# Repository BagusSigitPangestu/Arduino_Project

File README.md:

# Arduino Project

Repository ini berisi beberapa proyek Arduino yang telah dibuat selama kuliah.

## 🔧 Tips Mengatasi Port Arduino Tidak Terdeteksi di Linux

Jika port serial tidak terdeteksi saat menggunakan Arduino di Linux, coba jalankan perintah berikut secara berurutan:

### 1️⃣ Hapus Udev Rules yang Bermasalah
Jalankan perintah berikut untuk menghapus aturan `udev` yang dapat menyebabkan konflik:
```bash
for f in /usr/lib/udev/rules.d/*brltty*.rules; do
    sudo ln -s /dev/null "/etc/udev/rules.d/$(basename "$f")"
done
sudo udevadm control --reload-rules
```

### 2️⃣ Nonaktifkan Layanan `brltty`
Nonaktifkan `brltty` (Braille Terminal Daemon) yang dapat mengganggu koneksi serial:
```bash
sudo systemctl mask brltty.path
```

### 3️⃣ Tambahkan Pengguna ke Grup `dialout`
Pastikan akun pengguna memiliki akses ke perangkat serial dengan menambahkan ke grup `dialout`:
```bash
sudo usermod -a -G dialout $USER
```
Setelah itu, logout dan login kembali agar perubahan diterapkan.

---

📌 **Referensi:**  
[Unable to use USB dongle based on USB-serial converter](https://unix.stackexchange.com/questions/670636/unable-to-use-usb-dongle-based-on-usb-serial-converter-chip/670637#670637)

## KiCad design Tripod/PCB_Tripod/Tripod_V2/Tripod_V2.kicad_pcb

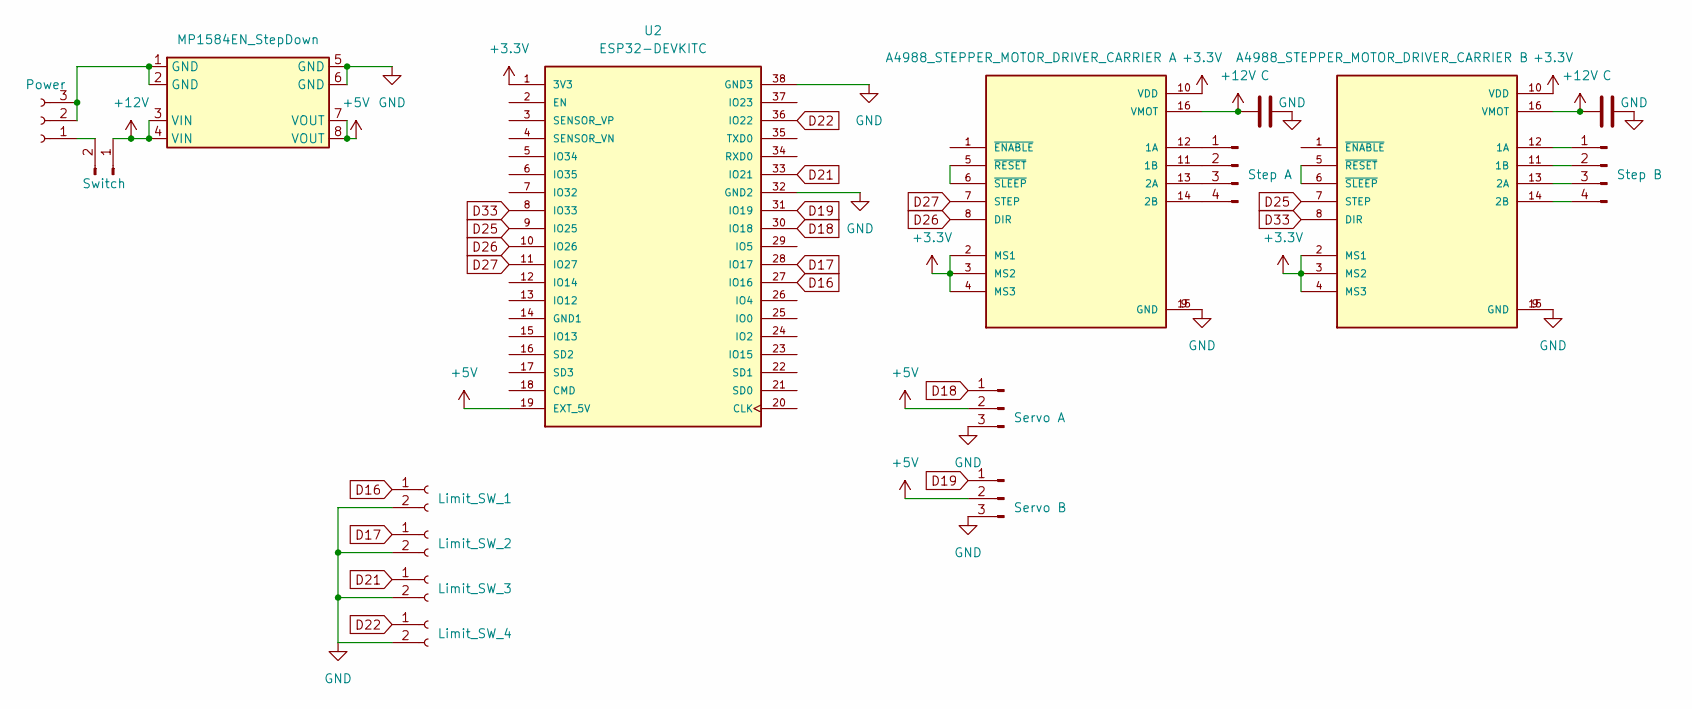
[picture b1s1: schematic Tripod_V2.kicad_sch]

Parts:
C1, C2: C; CP_Radial_D5.0mm_P2.50mm
J1: Power; BarrelJack_Horizontal
J2: Switch; TE_282837-2
J3: Servo A; PinHeader_1x03_P2.54mm_Vertical
J4: Servo B; PinHeader_1x03_P2.54mm_Vertical
J5: Step A; JST_EH_B4B-EH-A_1x04_P2.50mm_Vertical
J6: Step B; JST_EH_B4B-EH-A_1x04_P2.50mm_Vertical
J7: Limit_SW_1; PinHeader_1x02_P2.54mm_Vertical
J8: Limit_SW_2; PinHeader_1x02_P2.54mm_Vertical
J9: Limit_SW_3; PinHeader_1x02_P2.54mm_Vertical
J10: Limit_SW_4; PinHeader_1x02_P2.54mm_Vertical
U1: MP1584EN_StepDown
U2: ESP32-DEVKITC; MODULE_ESP32-DEVKITC; PARTREV N/A
U3: A4988_STEPPER_MOTOR_DRIVER_CARRIER A; MODULE_A4988_STEPPER_MOTOR_DRIVER_CARRIER
U4: A4988_STEPPER_MOTOR_DRIVER_CARRIER B; MODULE_A4988_STEPPER_MOTOR_DRIVER_CARRIER

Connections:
+3V3: U2.1 (3V3), U3.2 (MS1), U3.3 (MS2), U3.4 (MS3), U3.10 (VDD), U4.2 (MS1), U4.3 (MS2), U4.4 (MS3), U4.10 (VDD)
+5V: J3.2, J4.2, U1.7 (VOUT), U1.8 (VOUT), U2.19 (EXT_5V)
+12V: C1.1, C2.1, J2.1, U1.3 (VIN), U1.4 (VIN), U3.16 (VMOT), U4.16 (VMOT)
D16: J7.1, U2.27 (IO16)
D17: J8.1, U2.28 (IO17)
D18: J3.1, U2.30 (IO18)
D19: J4.1, U2.31 (IO19)
D21: J9.1, U2.33 (IO21)
D22: J10.1, U2.36 (IO22)
D25: U2.9 (IO25), U4.7 (STEP)
D26: U2.10 (IO26), U3.8 (DIR)
D27: U2.11 (IO27), U3.7 (STEP)
D33: U2.8 (IO33), U4.8 (DIR)
GND: C1.2, C2.2, J3.3, J4.3, J7.2, J8.2, J9.2, J10.2, U1.5 (GND), U1.6 (GND), U2.32 (GND2), U2.38 (GND3), U3.9 (GND), U3.15 (GND), U4.9 (GND), U4.15 (GND)
unnamed: J1.1, J2.2
unnamed: J1.2, J1.3, U1.1 (GND), U1.2 (GND)
unnamed: J5.1, U3.12 (1A)
unnamed: J5.2, U3.11 (1B)
unnamed: J5.3, U3.13 (2A)
unnamed: J5.4, U3.14 (2B)
unnamed: J6.1, U4.12 (1A)
unnamed: J6.2, U4.11 (1B)
unnamed: J6.3, U4.13 (2A)
unnamed: J6.4, U4.14 (2B)
unnamed: U3.5 (~RESET), U3.6 (~SLEEP)
unnamed: U4.5 (~RESET), U4.6 (~SLEEP)

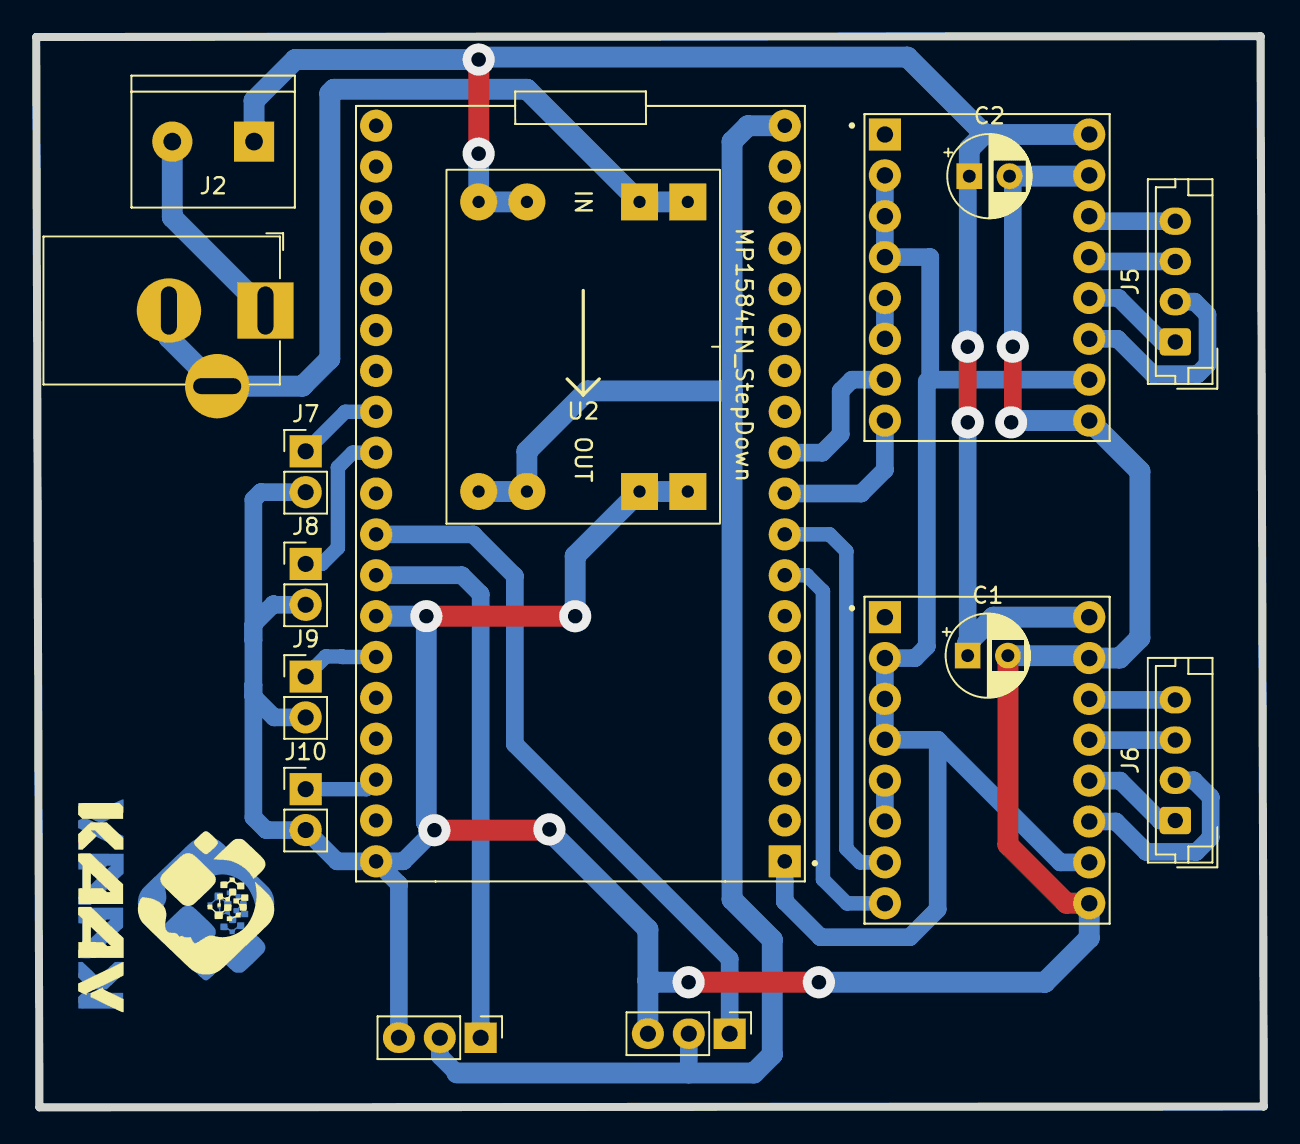
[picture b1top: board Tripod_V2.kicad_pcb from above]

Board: 2 copper layers, 76.3 x 66.6 mm, 16 parts (0 on the bottom side), 26 nets.

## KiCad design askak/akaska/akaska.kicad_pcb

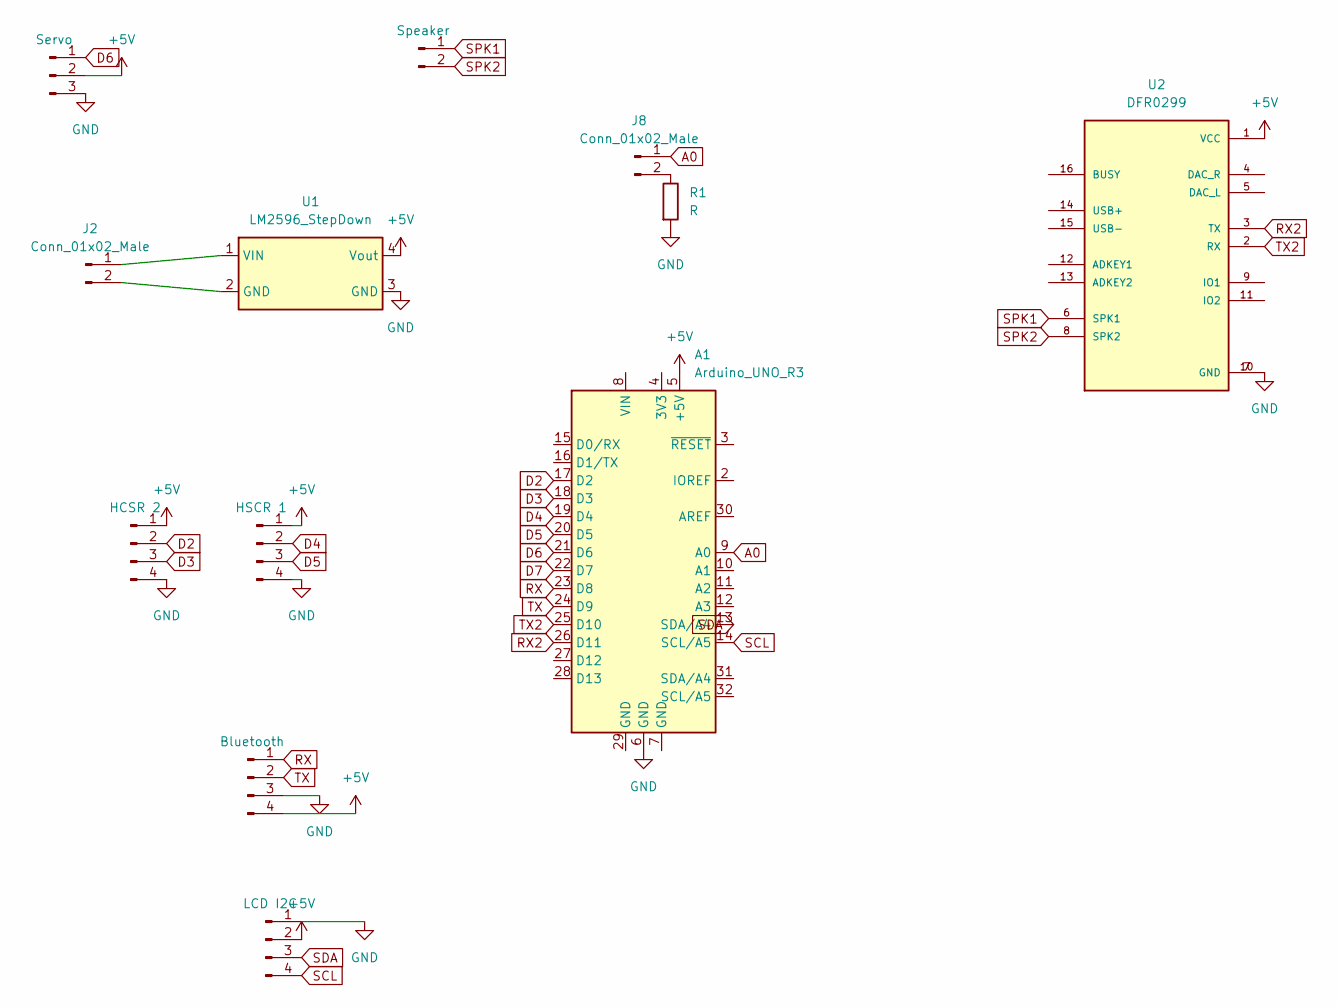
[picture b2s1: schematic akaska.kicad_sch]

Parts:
A1: Arduino_UNO_R3
J1: Servo; PinHeader_1x03_P2.54mm_Vertical
J2: Conn_01x02_Male; TerminalBlock_Altech_AK300-2_P5.00mm
J3: HCSR 2; PinHeader_1x04_P2.54mm_Vertical
J4: Bluetooth; PinSocket_1x04_P2.54mm_Vertical
J5: HSCR 1; PinHeader_1x04_P2.54mm_Vertical
J6: LCD I2C; PinHeader_1x04_P2.54mm_Vertical
J7: Speaker; PinHeader_1x02_P2.54mm_Vertical
J8: Conn_01x02_Male; LED_D3.0mm
R1: R; R_Axial_DIN0207_L6.3mm_D2.5mm_P15.24mm_Horizontal
U1: LM2596_StepDown; StepDown_LM2596
U2: DFR0299; MODULE_DFR0299

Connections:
+5V: A1.5 (+5V), J1.2, J3.1, J4.4, J5.1, J6.2, U1.4 (Vout), U2.1 (VCC)
A0: A1.9 (A0), J8.1
D2: A1.17 (D2), J3.2
D3: A1.18 (D3), J3.3
D4: A1.19 (D4), J5.2
D5: A1.20 (D5), J5.3
D6: A1.21 (D6), J1.1
D7: A1.22 (D7)
GND: A1.6 (GND), J1.3, J3.4, J4.3, J5.4, J6.1, R1.2, U1.3 (GND), U2.7 (GND), U2.10 (GND)
unnamed: J2.1, U1.1 (VIN)
unnamed: J2.2, U1.2 (GND)
unnamed: J8.2, R1.1
RX: A1.23 (D8), J4.1
RX2: A1.26 (D11), U2.3 (TX)
SCL: A1.14 (SCL/A5), J6.4
SDA: A1.13 (SDA/A4), J6.3
SPK1: J7.1, U2.6 (SPK1)
SPK2: J7.2, U2.8 (SPK2)
TX: A1.24 (D9), J4.2
TX2: A1.25 (D10), U2.2 (RX)

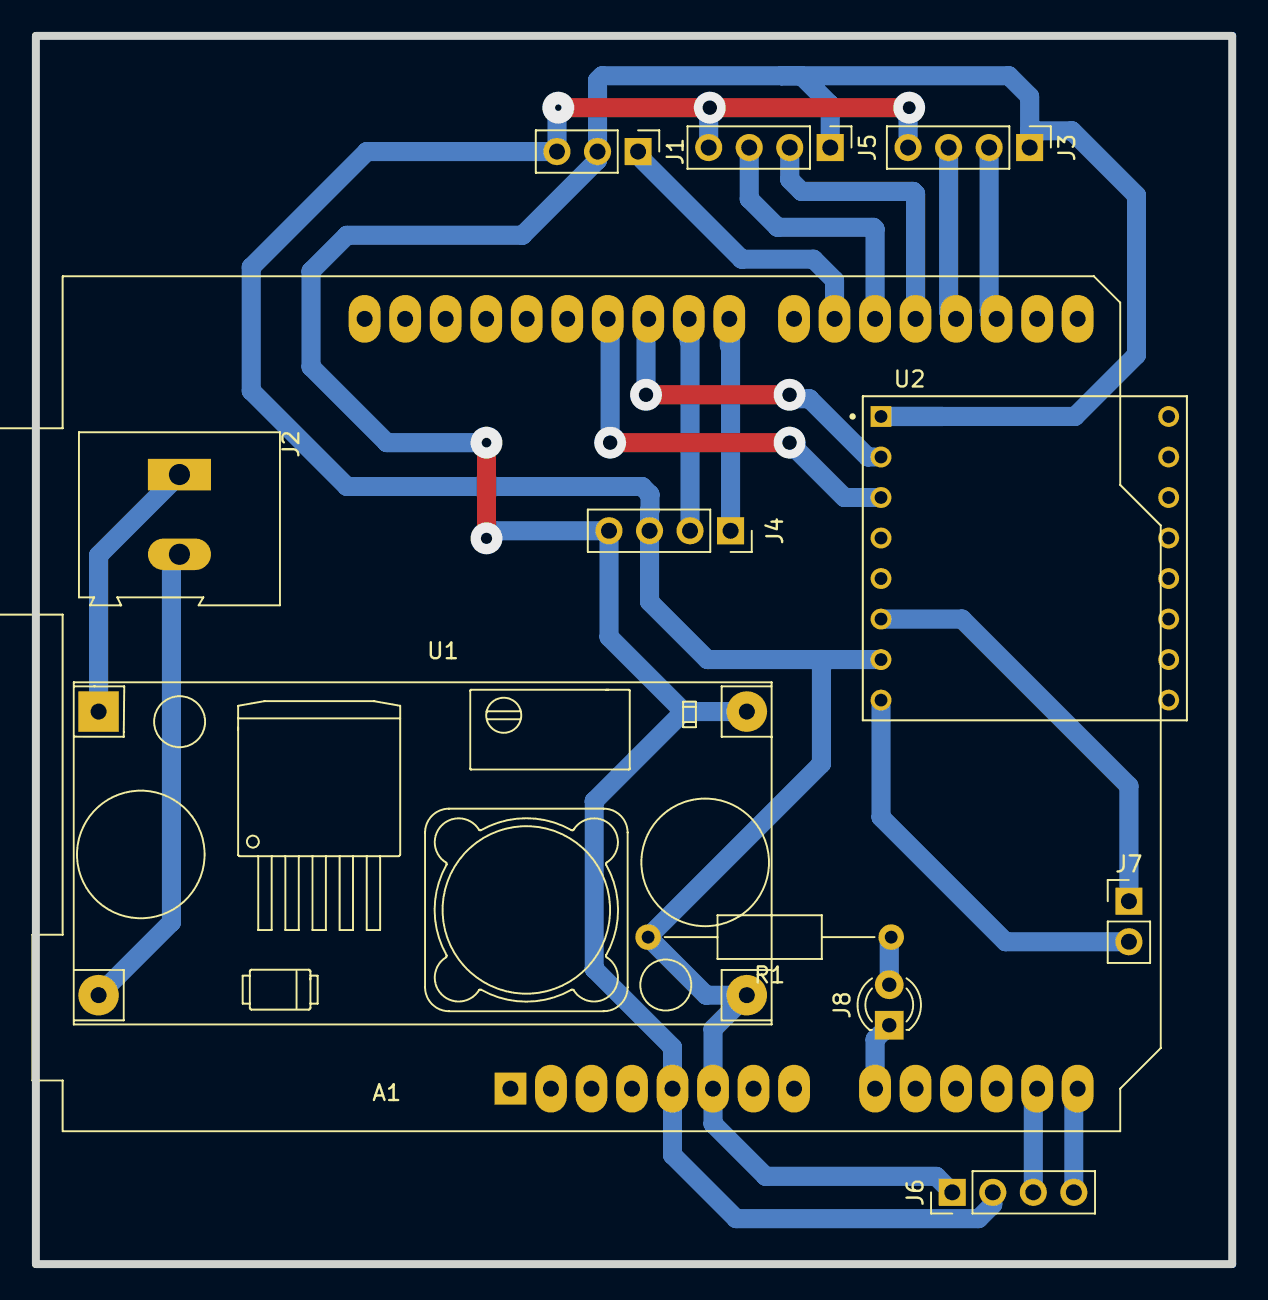
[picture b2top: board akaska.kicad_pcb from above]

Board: 2 copper layers, 75.0 x 77.0 mm, 12 parts (0 on the bottom side), 19 nets.

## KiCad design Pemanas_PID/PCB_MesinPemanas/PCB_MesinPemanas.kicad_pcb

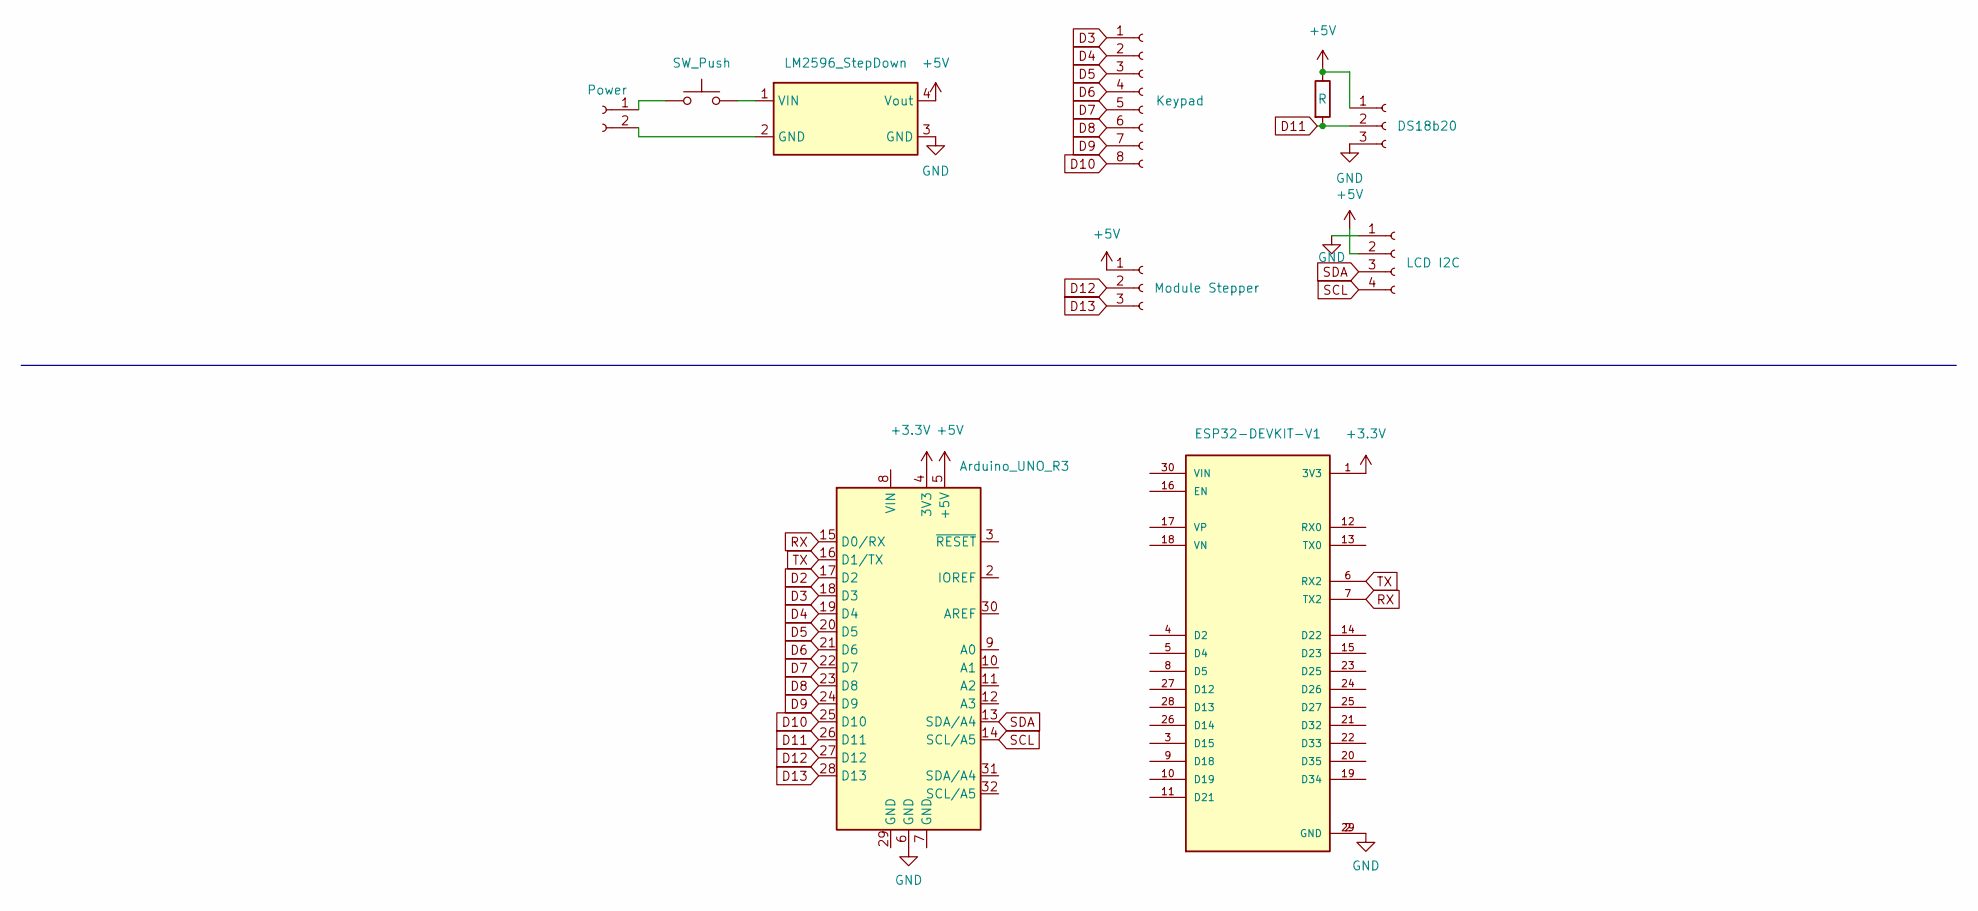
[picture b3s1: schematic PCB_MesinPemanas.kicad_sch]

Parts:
A1: Arduino_UNO_R3
J1: Power; TE_282837-2
J2: Keypad; PinSocket_1x08_P2.54mm_Vertical
J3: Module Stepper; PinSocket_1x03_P2.54mm_Vertical
J4: DS18b20; PinSocket_1x03_P2.54mm_Vertical
J5: LCD I2C; PinSocket_1x04_P2.54mm_Vertical
R1: R; R_Axial_DIN0207_L6.3mm_D2.5mm_P10.16mm_Horizontal
SW1: SW_Push; TE_282837-2
U1: LM2596_StepDown; StepDown_LM2596
U2: ESP32-DEVKIT-V1; MODULE_ESP32_DEVKIT_V1; PARTREV N/A

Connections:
+3V3: A1.4 (3V3), U2.1 (3V3)
+5V: A1.5 (+5V), J3.1, J4.1, J5.2, R1.1, U1.4 (Vout)
D2: A1.17 (D2); also elsewhere on the board
D3: A1.18 (D3), J2.1
D4: A1.19 (D4), J2.2
D5: A1.20 (D5), J2.3
D6: A1.21 (D6), J2.4
D7: A1.22 (D7), J2.5
D8: A1.23 (D8), J2.6
D9: A1.24 (D9), J2.7
D10: A1.25 (D10), J2.8
D11: A1.26 (D11), J4.2, R1.2
D12: A1.27 (D12), J3.2
D13: A1.28 (D13), J3.3
GND: A1.6 (GND), J4.3, J5.1, U1.3 (GND), U2.2 (GND), U2.29 (GND); also elsewhere on the board
unnamed: J1.1, SW1.1
unnamed: J1.2, U1.2 (GND)
unnamed: SW1.2, U1.1 (VIN)
RX: A1.15 (D0/RX), U2.7 (TX2)
SCL: A1.14 (SCL/A5), J5.4
SDA: A1.13 (SDA/A4), J5.3
TX: A1.16 (D1/TX), U2.6 (RX2)

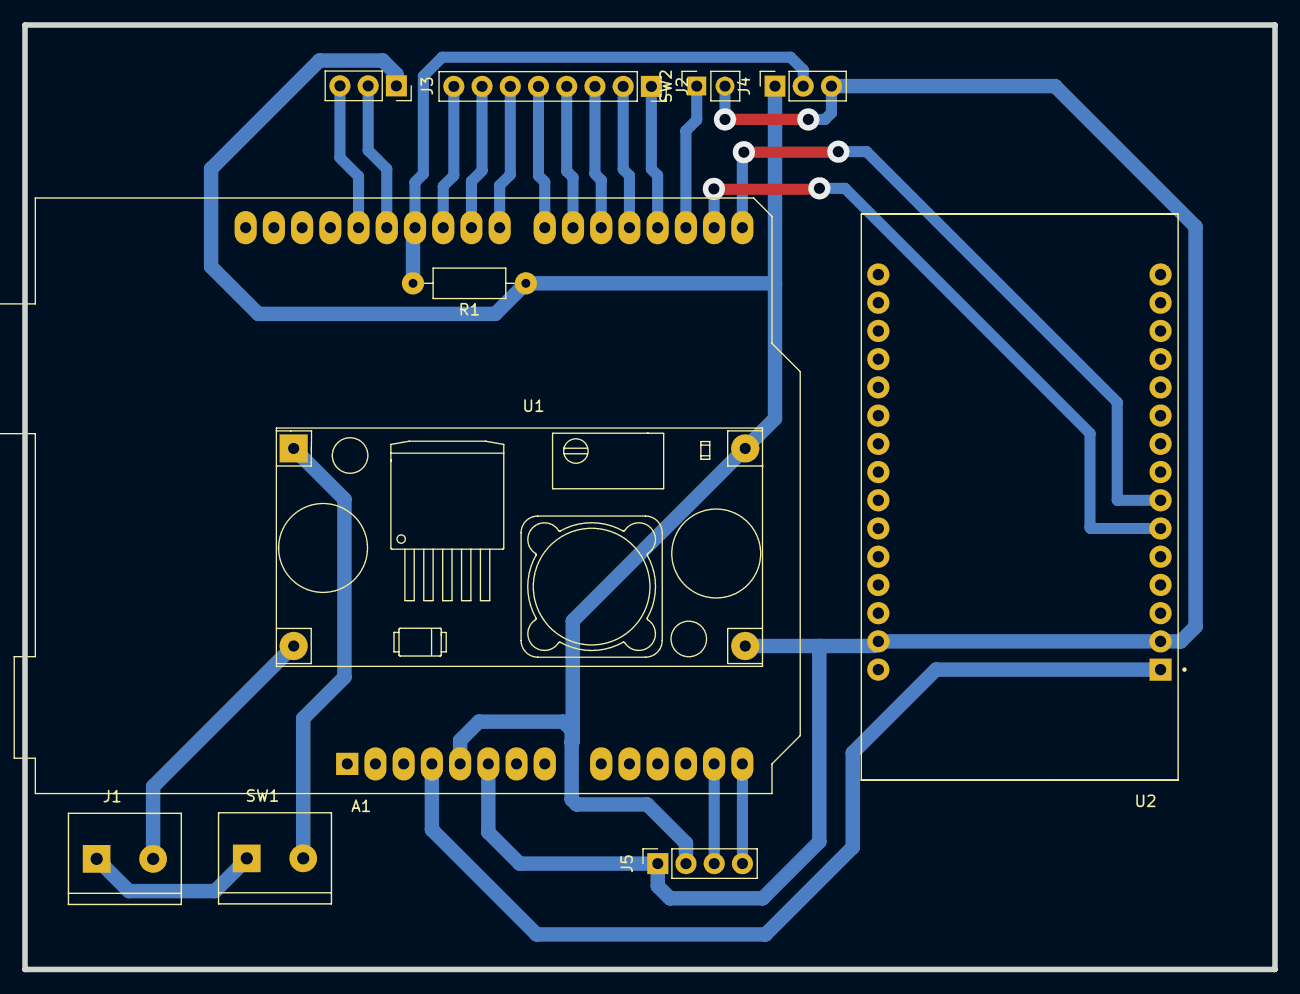
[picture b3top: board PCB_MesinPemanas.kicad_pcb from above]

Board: 2 copper layers, 112.5 x 85.0 mm, 11 parts (0 on the bottom side), 22 nets.

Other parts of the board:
SW2: Limit Swich; PinSocket_1x02_P2.54mm_Vertical

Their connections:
D2: SW2.1; also elsewhere on the board
GND: SW2.2; also elsewhere on the board

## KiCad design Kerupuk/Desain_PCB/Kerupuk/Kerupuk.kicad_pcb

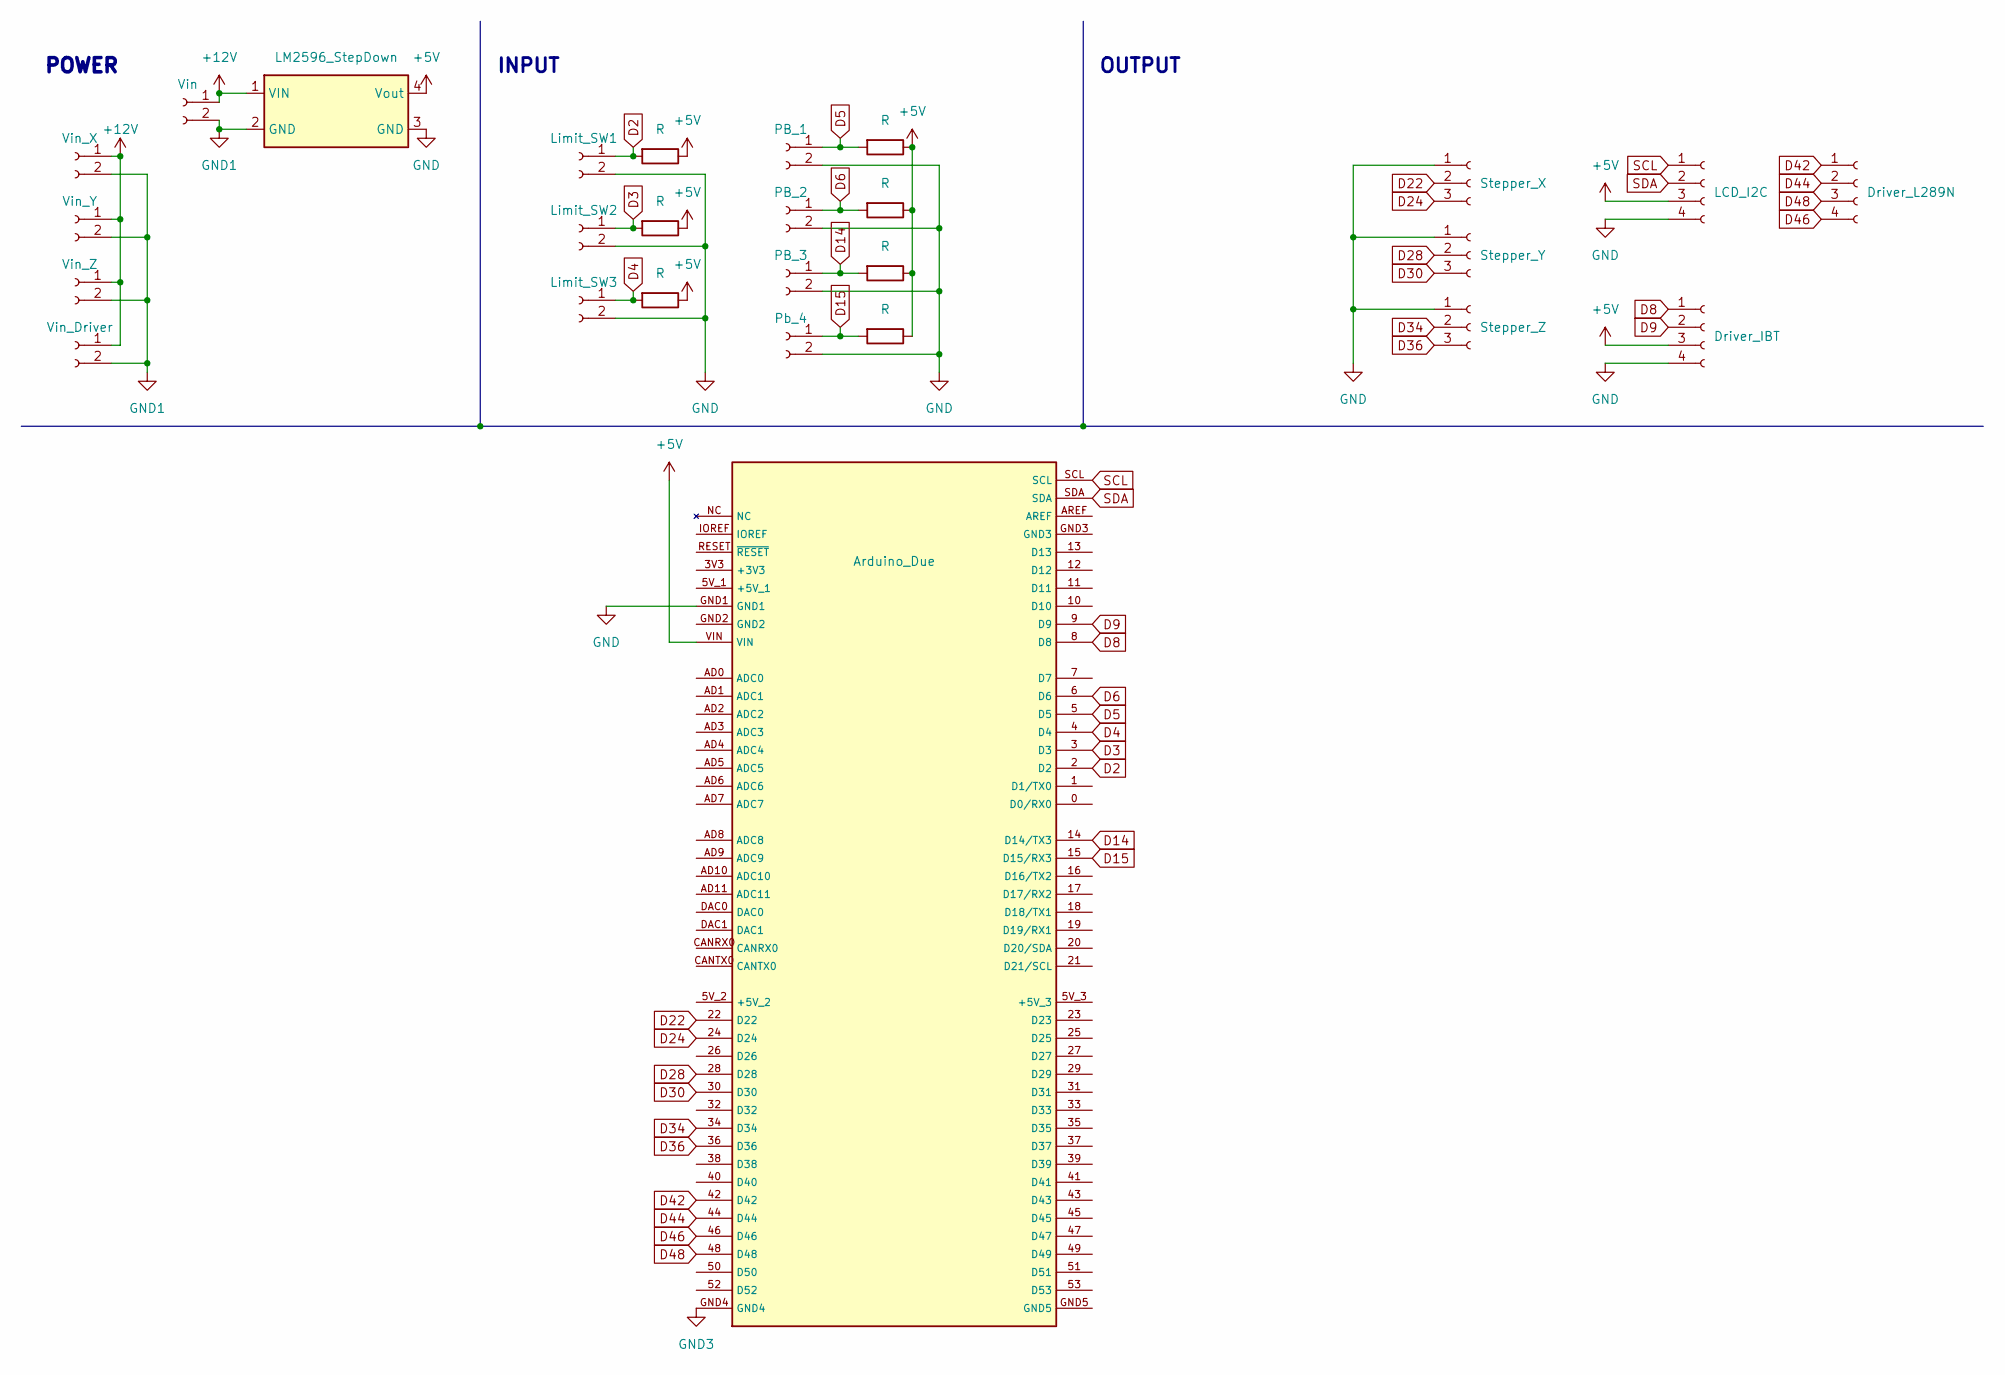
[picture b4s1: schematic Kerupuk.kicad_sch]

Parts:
J1: Vin; TE_282837-2
J2: Limit_SW1; PinSocket_1x02_P2.54mm_Vertical
J3: Limit_SW2; PinSocket_1x02_P2.54mm_Vertical
J4: Limit_SW3; PinSocket_1x02_P2.54mm_Vertical
J5: PB_1; PinSocket_1x02_P2.54mm_Vertical
J6: PB_2; PinSocket_1x02_P2.54mm_Vertical
J7: Stepper_X; PinSocket_1x03_P2.54mm_Vertical
J8: Stepper_Y; PinSocket_1x03_P2.54mm_Vertical
J9: Stepper_Z; PinSocket_1x03_P2.54mm_Vertical
J10: LCD_I2C; PinSocket_1x04_P2.54mm_Vertical
J11: Driver_IBT; PinSocket_1x04_P2.54mm_Vertical
J12: Vin_X; TE_282837-2
J13: Vin_Y; TE_282837-2
J14: Vin_Z; TE_282837-2
J15: PB_3; PinSocket_1x02_P2.54mm_Vertical
J16: Pb_4; PinSocket_1x02_P2.54mm_Vertical
J17: Driver_L289N; PinSocket_1x04_P2.54mm_Vertical
J18: Vin_Driver; TE_282837-2
R1, R2, R3, R4, R5, R6, R7: R; R_Axial_DIN0204_L3.6mm_D1.6mm_P7.62mm_Horizontal
U1: Arduino_Due
U2: LM2596_StepDown; StepDown_LM2596

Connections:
+5V: J10.3, J11.3, R1.1, R2.1, R3.1, R4.1, R5.1, R6.1, R7.1, U1.VIN, U2.4 (Vout)
+12V: J1.1, J12.1, J13.1, J14.1, J18.1, U2.1 (VIN)
D2: J2.1, R1.2, U1.2 (D2)
D3: J3.1, R2.2, U1.3 (D3)
D4: J4.1, R3.2, U1.4 (D4)
D5: J5.1, R4.2, U1.5 (D5)
D6: J6.1, R5.2, U1.6 (D6)
D8: J11.1, U1.8 (D8)
D9: J11.2, U1.9 (D9)
D14: J15.1, R6.2, U1.14 (D14/TX3)
D15: J16.1, R7.2, U1.15 (D15/RX3)
D22: J7.2, U1.22 (D22)
D24: J7.3, U1.24 (D24)
D28: J8.2, U1.28 (D28)
D30: J8.3, U1.30 (D30)
D34: J9.2, U1.34 (D34)
D36: J9.3, U1.36 (D36)
D42: J17.1, U1.42 (D42)
D44: J17.2, U1.44 (D44)
D46: J17.4, U1.46 (D46)
D48: J17.3, U1.48 (D48)
GND: J2.2, J3.2, J4.2, J5.2, J6.2, J7.1, J8.1, J9.1, J10.4, J11.4, J15.2, J16.2, U1.GND1, U2.3 (GND)
GND1: J1.2, J12.2, J13.2, J14.2, J18.2, U2.2 (GND)
GND3: U1.GND4
SCL: J10.1, U1.SCL
SDA: J10.2, U1.SDA

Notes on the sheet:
INPUT
OUTPUT
POWER

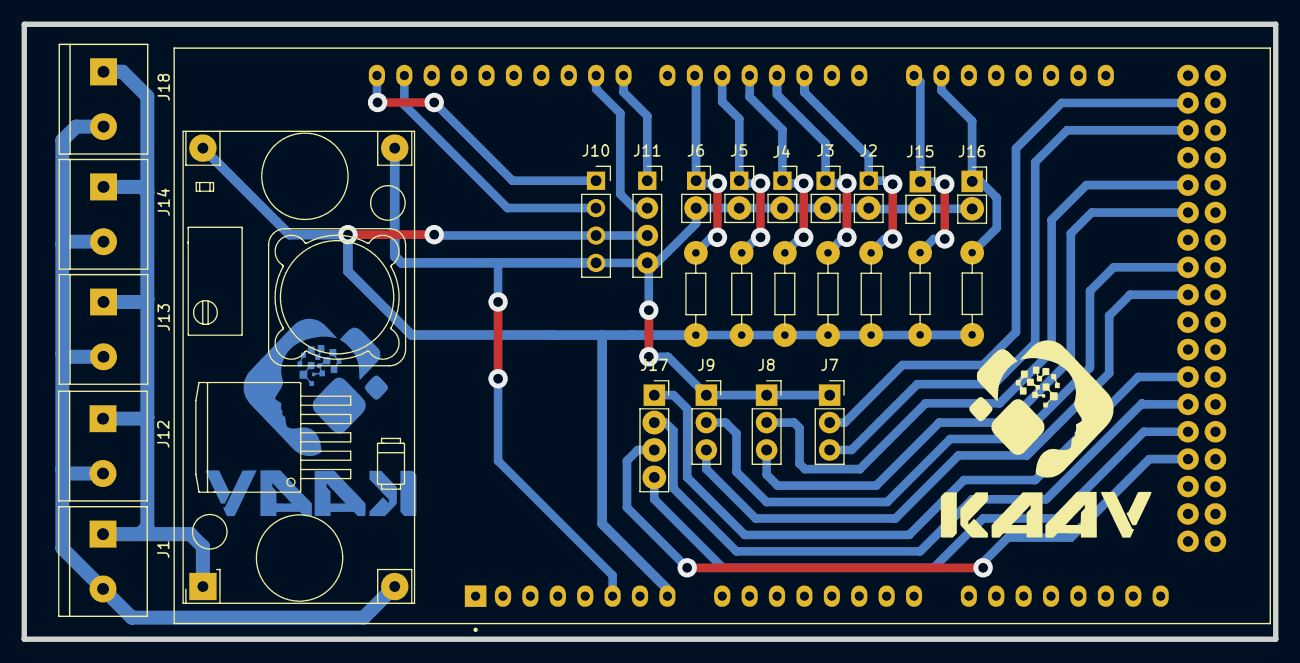
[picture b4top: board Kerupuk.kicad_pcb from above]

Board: 2 copper layers, 116.0 x 57.0 mm, 27 parts (0 on the bottom side), 25 nets.

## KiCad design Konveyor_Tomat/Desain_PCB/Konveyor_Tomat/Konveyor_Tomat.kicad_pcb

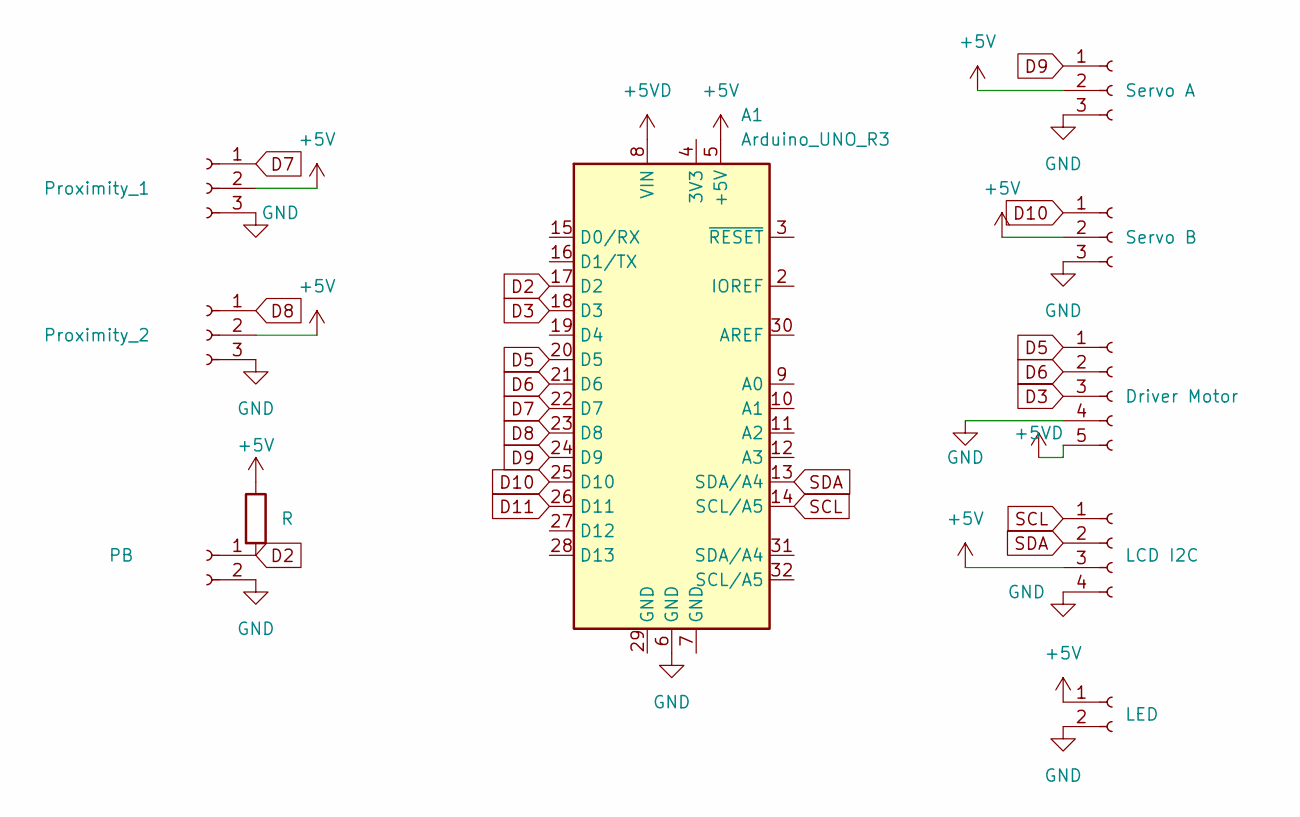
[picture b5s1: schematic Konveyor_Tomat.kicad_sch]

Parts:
A1: Arduino_UNO_R3
J1: Proximity_1; PinHeader_1x03_P2.54mm_Vertical
J2: Proximity_2; PinHeader_1x03_P2.54mm_Vertical
J3: PB; PinHeader_1x02_P2.54mm_Vertical
J4: Servo A; PinHeader_1x03_P2.54mm_Vertical
J5: Servo B; PinHeader_1x03_P2.54mm_Vertical
J6: Driver Motor; PinHeader_1x05_P2.54mm_Vertical
J7: LCD I2C; PinHeader_1x04_P2.54mm_Vertical
J8: LED; PinHeader_1x02_P2.54mm_Vertical
R1: R; R_Axial_DIN0207_L6.3mm_D2.5mm_P10.16mm_Horizontal

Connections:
+5V: A1.5 (+5V), J1.2, J2.2, J4.2, J5.2, J7.3, J8.1, R1.1
+5VD: A1.8 (VIN), J6.5
D2: A1.17 (D2), J3.1, R1.2
D3: A1.18 (D3), J6.3
D5: A1.20 (D5), J6.1
D6: A1.21 (D6), J6.2
D7: A1.22 (D7), J1.1
D8: A1.23 (D8), J2.1
D9: A1.24 (D9), J4.1
D10: A1.25 (D10), J5.1
D11: A1.26 (D11)
GND: A1.6 (GND), J1.3, J2.3, J3.2, J4.3, J5.3, J6.4, J7.4, J8.2
SCL: A1.14 (SCL/A5), J7.1
SDA: A1.13 (SDA/A4), J7.2

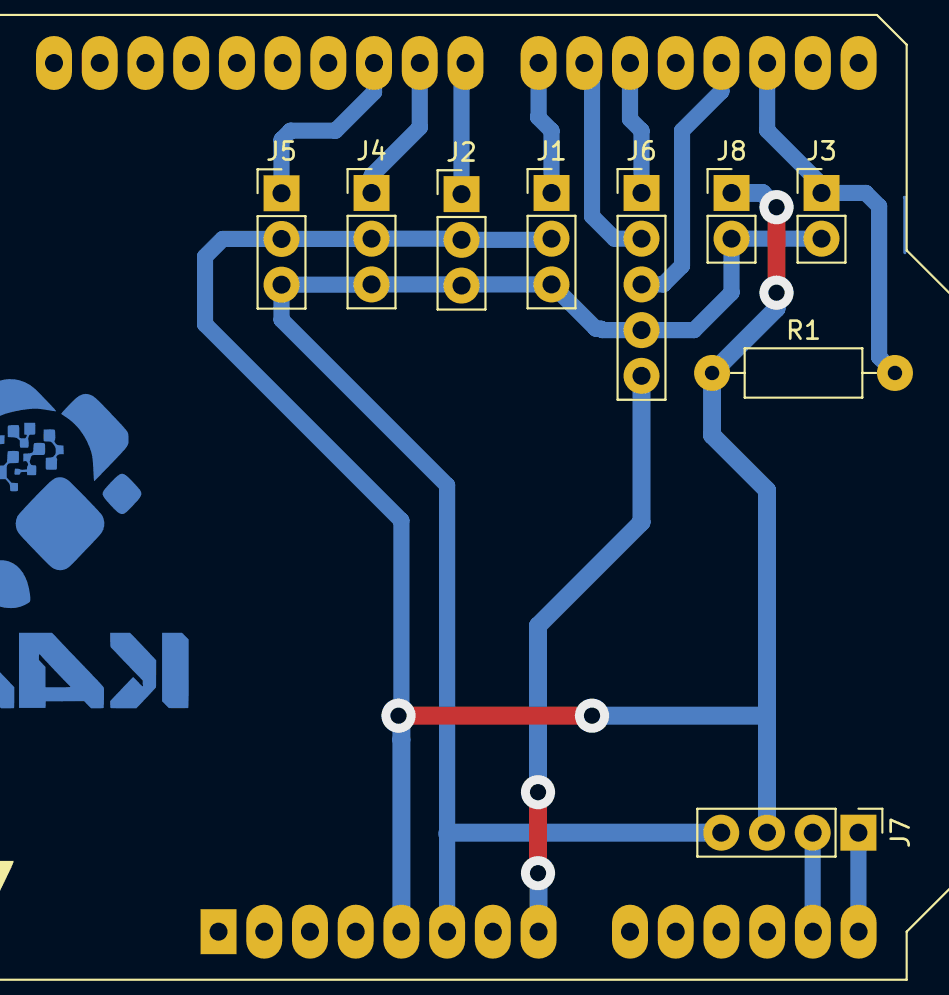
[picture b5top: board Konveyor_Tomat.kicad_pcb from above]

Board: 2 copper layers, 10 parts (0 on the bottom side), 13 nets.

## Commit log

2024-02-16 coba commit
